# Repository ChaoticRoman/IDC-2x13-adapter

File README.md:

# IDC 2x13 connector adapter to screw terminals

Kicad project, single sided board, suitable for home manufacturing.

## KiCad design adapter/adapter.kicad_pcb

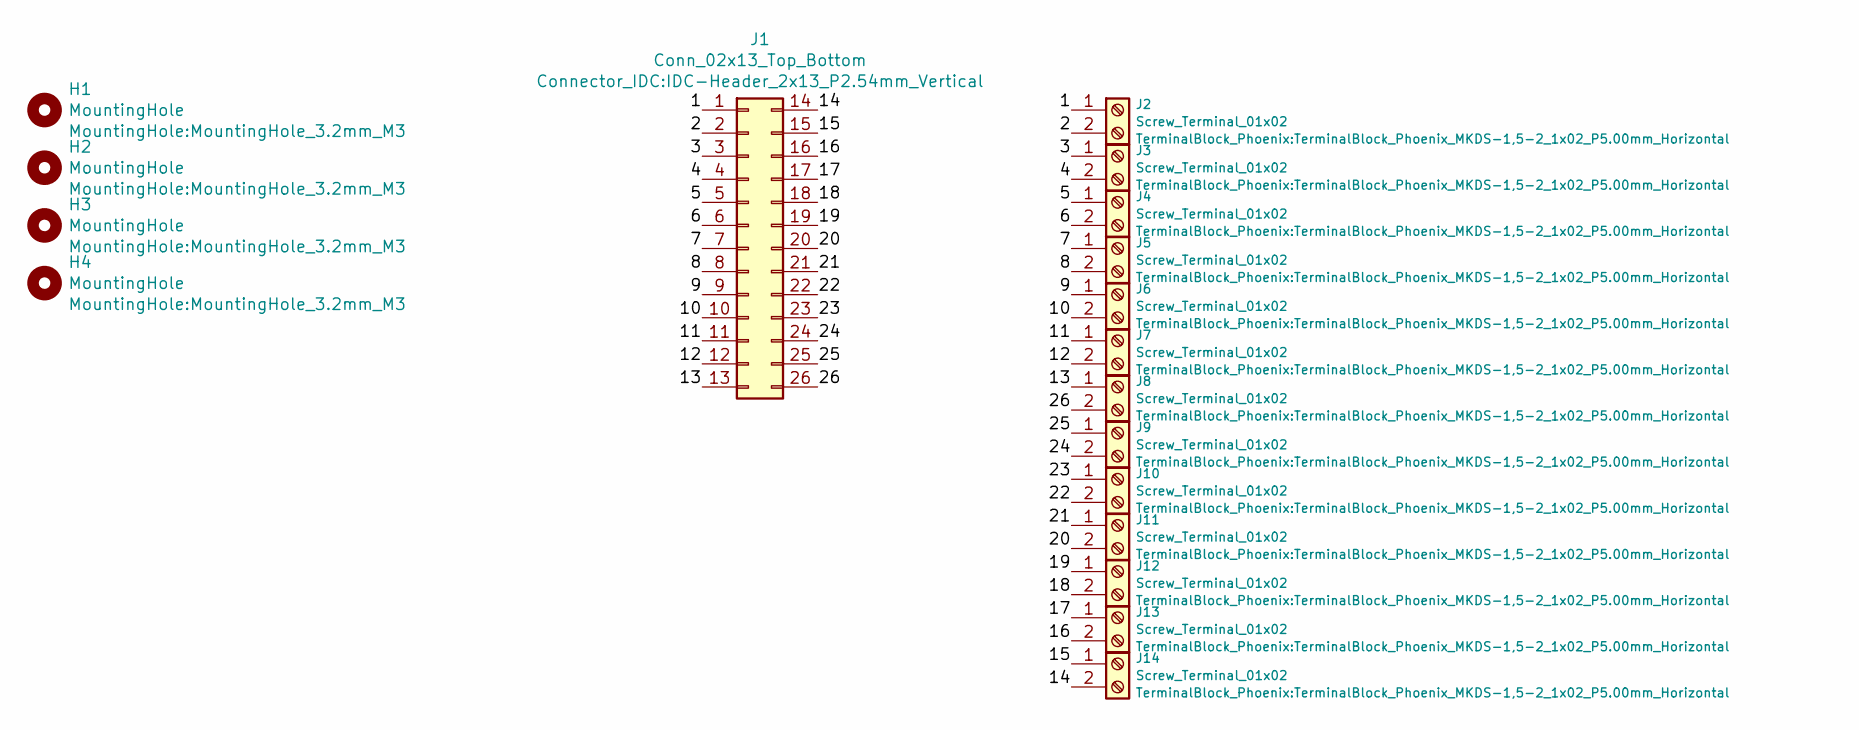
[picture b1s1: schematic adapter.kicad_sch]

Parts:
H1, H2, H3, H4: MountingHole; MountingHole_3.2mm_M3
J1: Conn_02x13_Top_Bottom; IDC-Header_2x13_P2.54mm_Vertical
J2, J3, J4, J5, J6, J7, J8, J9, J10, J11, J12, J13, J14: Screw_Terminal_01x02; TerminalBlock_Phoenix_MKDS-1,5-2_1x02_P5.00mm_Horizontal

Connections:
/1: J1.1, J2.1
/2: J1.2, J2.2
/3: J1.3, J3.1
/4: J1.4, J3.2
/5: J1.5, J4.1
/6: J1.6, J4.2
/7: J1.7, J5.1
/8: J1.8, J5.2
/9: J1.9, J6.1
/10: J1.10, J6.2
/11: J1.11, J7.1
/12: J1.12, J7.2
/13: J1.13, J8.1
/14: J1.14, J14.2
/15: J1.15, J14.1
/16: J1.16, J13.2
/17: J1.17, J13.1
/18: J1.18, J12.2
/19: J1.19, J12.1
/20: J1.20, J11.2
/21: J1.21, J11.1
/22: J1.22, J10.2
/23: J1.23, J10.1
/24: J1.24, J9.2
/25: J1.25, J9.1
/26: J1.26, J8.2

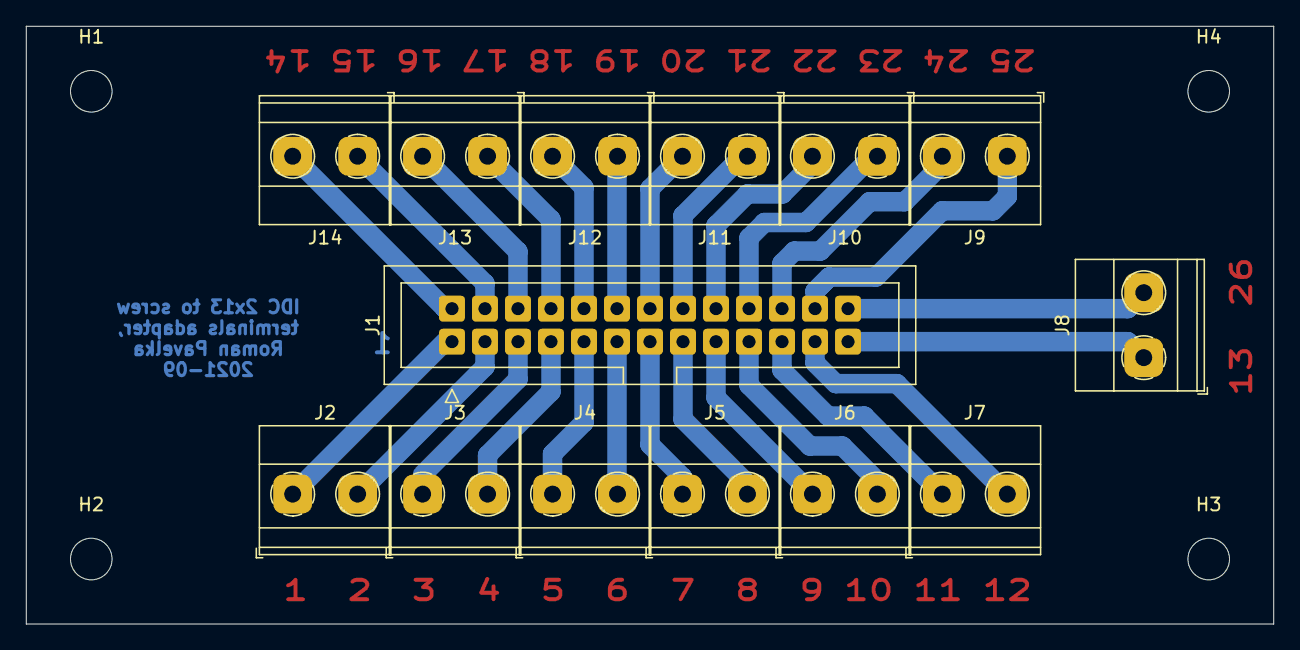
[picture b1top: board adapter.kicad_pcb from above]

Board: 2 copper layers, 96.0 x 46.0 mm, 18 parts (0 on the bottom side), 26 nets.

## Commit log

2021-09-03 Add gitignore
2021-09-03 Add unrouted board
2021-09-03 Finish routing
2021-09-03 Fix small mistakes
2024-12-23 Checked if it still works in KiCAD 8 and updated
2024-12-23 Added .gitignore and README
2025-11-27 Add license
